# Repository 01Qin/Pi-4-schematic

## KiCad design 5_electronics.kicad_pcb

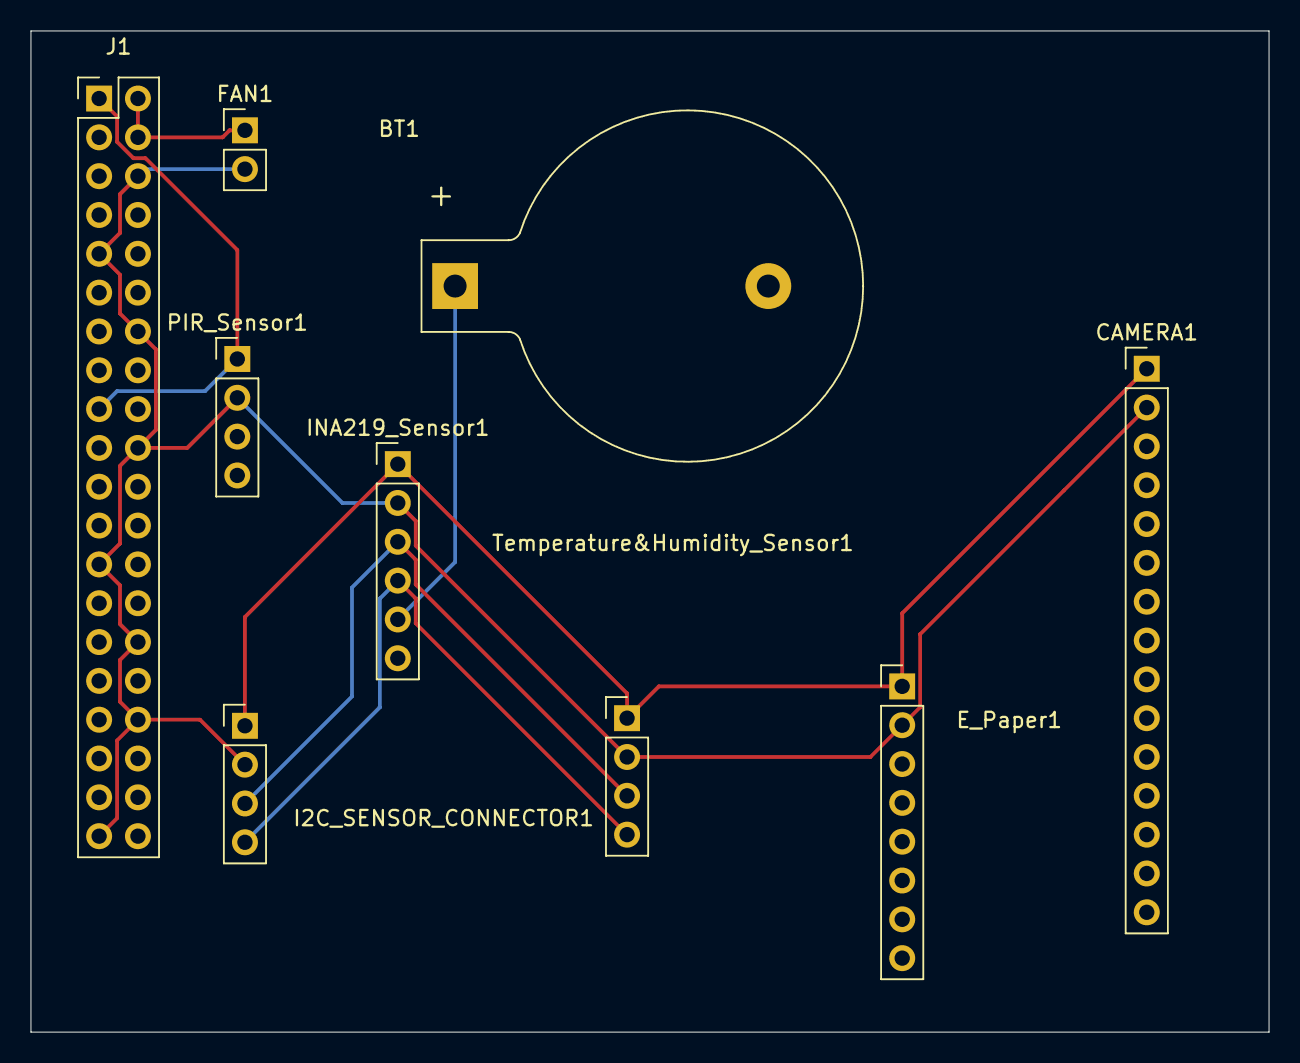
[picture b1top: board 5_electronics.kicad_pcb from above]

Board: 2 copper layers, 81.0 x 65.5 mm, 9 parts (0 on the bottom side), 7 nets.

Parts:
BT1: Battery_Cell; BatteryHolder_Keystone_103_1x20mm
CAMERA1: Conn_01x15; PinHeader_1x15_P2.54mm_Vertical
E_Paper1: Conn_01x08; PinHeader_1x08_P2.54mm_Vertical
FAN1: Conn_01x02; PinHeader_1x02_P2.54mm_Vertical
I2C_SENSOR_CONNECTOR1: Conn_01x04; PinHeader_1x04_P2.54mm_Vertical
INA219_Sensor1: Conn_01x06; PinHeader_1x06_P2.54mm_Vertical
J1: Conn_02x20_Odd_Even; PinHeader_2x20_P2.54mm_Vertical
PIR_Sensor1: Conn_01x04; PinHeader_1x04_P2.54mm_Vertical
Temperature&Humidity_Sensor1: Conn_01x04; PinHeader_1x04_P2.54mm_Vertical

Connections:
+3.3V: J1.1, J1.17, PIR_Sensor1.1
+3V3: CAMERA1.1, E_Paper1.1, I2C_SENSOR_CONNECTOR1.1, INA219_Sensor1.1, Temperature&Humidity_Sensor1.1
+5V: FAN1.1, J1.2, J1.4
BAT+: BT1.1 (+), INA219_Sensor1.5
GND: CAMERA1.2, E_Paper1.2, FAN1.2, I2C_SENSOR_CONNECTOR1.2, INA219_Sensor1.2, J1.6, J1.9, J1.14, J1.20, J1.25, J1.30, J1.34, J1.39, PIR_Sensor1.2, Temperature&Humidity_Sensor1.2
I2C_SCL: I2C_SENSOR_CONNECTOR1.4, INA219_Sensor1.4, Temperature&Humidity_Sensor1.4
I2C_SDA: I2C_SENSOR_CONNECTOR1.3, INA219_Sensor1.3, Temperature&Humidity_Sensor1.3

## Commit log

2026-04-26 Initial KiCad project
2026-04-26 Update page setting
2026-04-26 Add gpio pins
2026-04-26 Update gpio pins
2026-04-26 Remove kicad autosave files
2026-04-26 Assign footprint
2026-04-28 E-paper added
2026-04-28 Temperature & Humidity sensor connected
2026-04-29 Mark unused pins
2026-04-29 Update routing
